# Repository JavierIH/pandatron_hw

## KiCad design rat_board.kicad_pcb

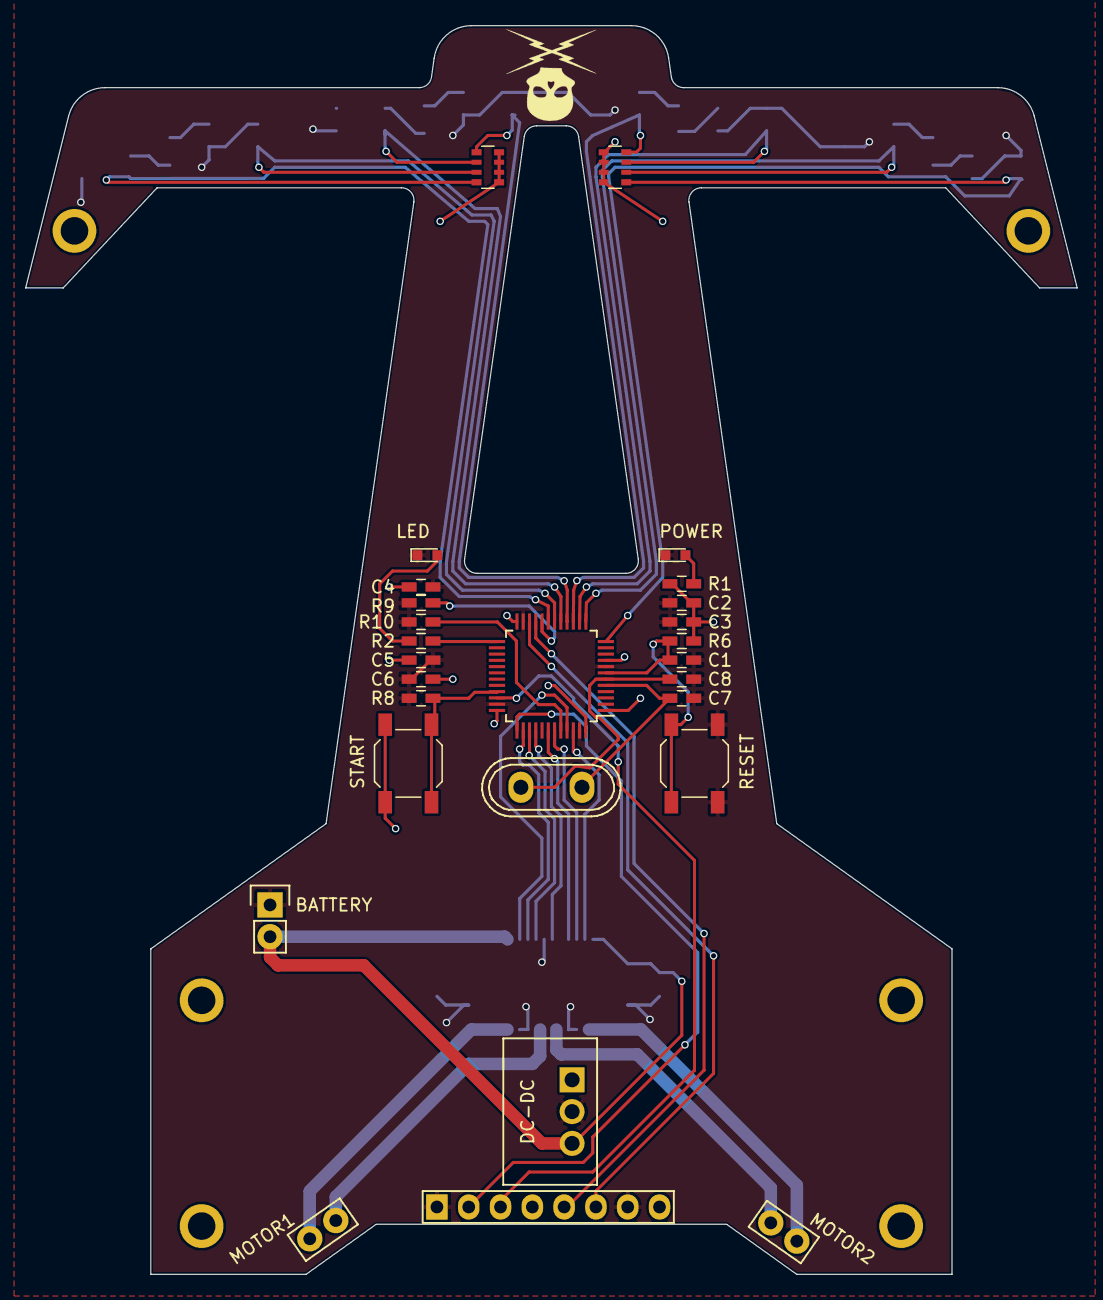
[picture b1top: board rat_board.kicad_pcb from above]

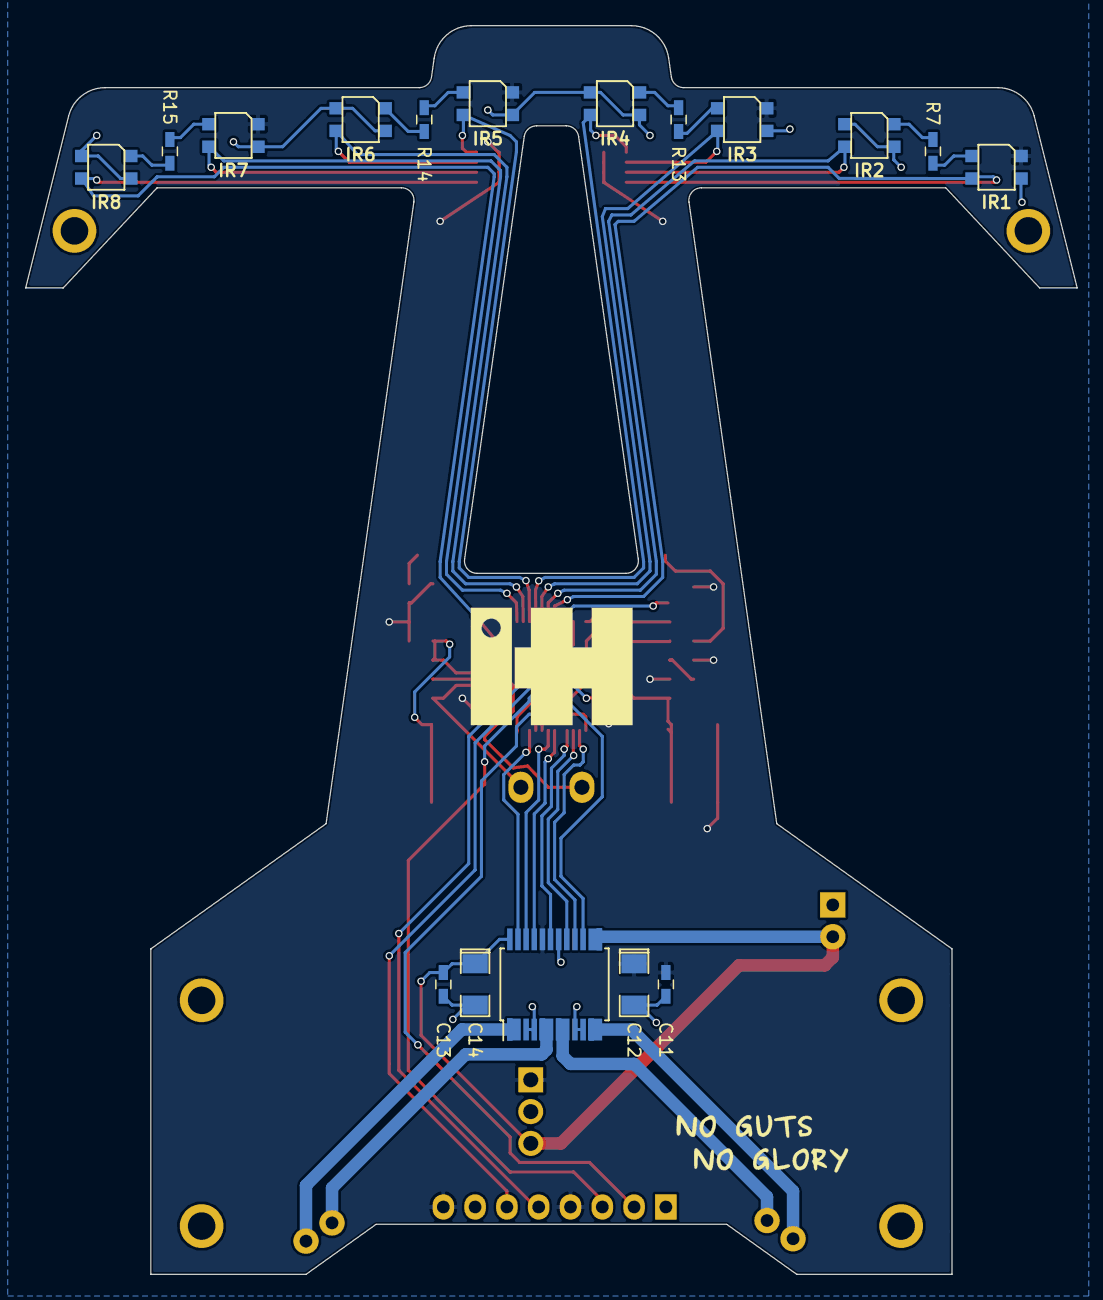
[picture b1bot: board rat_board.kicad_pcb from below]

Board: 2 copper layers, 84.0 x 99.8 mm, 38 parts (16 on the bottom side), 15 nets.

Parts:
BATTERY: CONN_01X02; Socket_Strip_Straight_1x02
C1, C6: 1uF; C_0603_HandSoldering
C2, C3: 100nF; C_0603_HandSoldering
C4: 4.7uF; C_0603_HandSoldering
C5: 10nF; C_0603_HandSoldering
C7, C8: 20p; C_0603_HandSoldering
C11, C13: 0.1uF; C_0603_HandSoldering
C12, C14: 10uF; SMD-1206_Pol
DC-DC: TR05S3V3
IR1, IR2, IR3, IR4, IR5, IR6, IR7, IR8: QRE1113; QRE1113GR
LED: LED_0; LED_0603
MOTOR1, MOTOR2: CONN_01X02; Socket_Strip_Straight_1x02
POWER: LED_Power; LED_0603
R1, R2: 100; C_0603_HandSoldering
R6, R8: 10k; C_0603_HandSoldering
R7, R13, R14, R15: 47; C_0603_HandSoldering
R9, R10: 100k; C_0603_HandSoldering
RESET: SW_PUSH_SMALL_H; SW_SPST_SKQG
START: START_BUTTON; SW_SPST_SKQG

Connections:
+3V3: C2.1, C3.1, C4.1, C5.1, C6.1, C11.1, C12.1, DC-DC.VO, IR1.1, IR3.1, IR5.1, IR7.1, R1.1, R6.1, START.1
+BATT: BATTERY.2, C13.1, C14.1, DC-DC.VI
/RESET: C1.1, R6.2, RESET.2
/UB_START: R8.2, START.2
GND: BATTERY.1, C1.2, C2.2, C3.2, C4.2, C5.2, C6.2, C7.2, C8.2, C11.2, C12.2, C13.2, C14.2, DC-DC.GND, IR1.4, IR2.2, IR2.4, IR3.4, IR4.2, IR4.4, IR5.4, IR6.2, IR6.4, IR7.4, IR8.2, IR8.4, LED.1, POWER.1, R8.1, R9.1, R10.2, RESET.1
unnamed: POWER.2, R1.2
unnamed: LED.2, R2.2
unnamed: IR2.1, R7.1
unnamed: IR1.2, R7.2
unnamed: IR4.1, R13.1
unnamed: IR3.2, R13.2
unnamed: IR6.1, R14.1
unnamed: IR5.2, R14.2
unnamed: IR8.1, R15.1
unnamed: IR7.2, R15.2

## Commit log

2017-11-01 releseable board
